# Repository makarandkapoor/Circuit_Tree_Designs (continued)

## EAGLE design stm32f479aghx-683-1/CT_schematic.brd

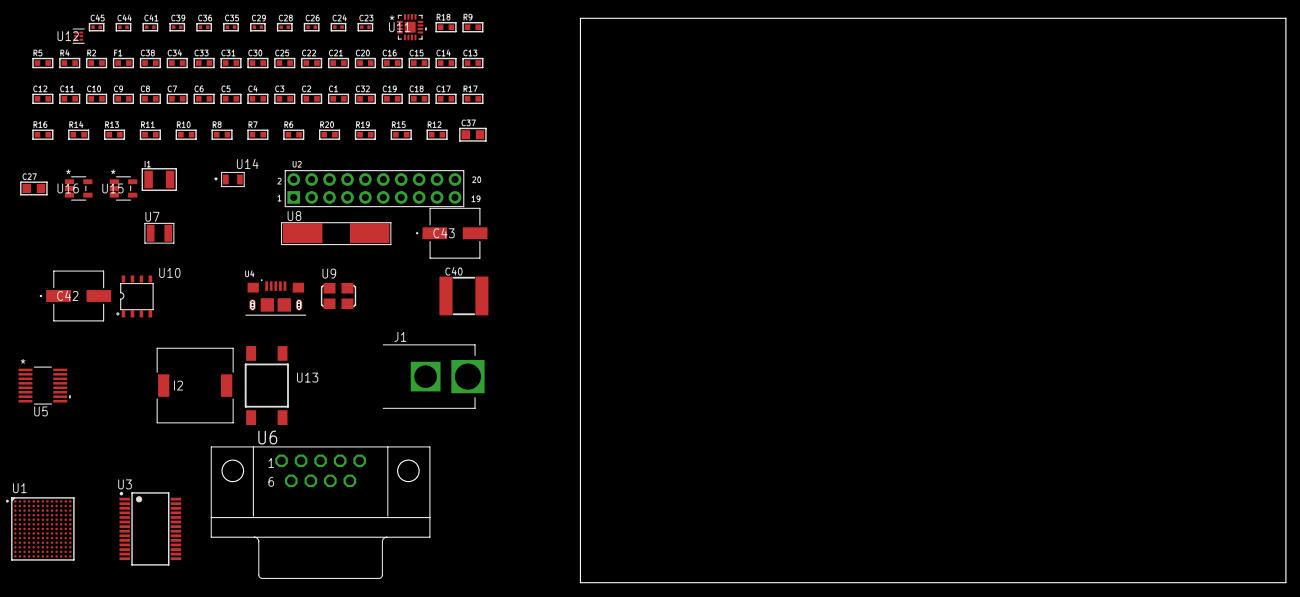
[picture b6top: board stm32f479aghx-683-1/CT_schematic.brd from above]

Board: 2 copper layers, 83 parts (0 on the bottom side), 59 nets, no tracks yet.

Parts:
C1, C21, C25, C30, C31, C33, C34, C38: 1e-06; C0603
C2, C3, C4, C5, C6, C7, C8, C9, C10, C11, C12, C13, C14, C15, C16, C22: 1e-07; C0603
C17: 4.7e-06; C0603
C18, C19: 2.2e-06; C0603
C20: 1e-08; C0603
C23, C24: 1e-11; C0402
C26, C28, C29, C39, C41: 1e-07; C0402
C27: 4.7e-06; C0805
C32: 2.2e-07; C0603
C35, C36, C44, C45: 1e-08; C0402
C37: 1e-05; C0805
C40: 6.8e-05; 2220
C42, C43: 0.0001; EXV-9H
F1: 240.0; L0603
I1: 1e-05; L1210
I2: 5.2e-06; DR1040
J1: PJ-037B; PJ-037B_PACKAGE
R2: 1000.0; R0603
R4, R5, R9: 4700.0; R0603
R6, R7, R8, R10, R11, R16, R17: 10000.0; R0603
R12: 100000.0; R0603
R13: 20000.0; R0603
R14: 91000.0; R0603
R15: 300000.0; R0603
R18: 9100.0; R0603
R19: 680000.0; R0603
R20: 120000.0; R0603
U1: STM32F479AGH6; UFBGA169
U2: arducam_ov2640; ARDUCAM
U3: FT232RL-REEL; SSOP-28
U4: 10118193-0001LF; FCI_10118193-0001LF
U5: LTC2804CGN-1#PBF; SSOP-16
U6: 182-009-113R531; 182-009-MALE
U7: ABS07-32.768KHZ-7-T
U8: ABLS-12.000MHZ-B4-T
U9: ASFL1-25MHZ-NCS; ASFL1
U10: idt74fct38072; IDT74FCT38072
U11: LTC3601EUD#PBF; QFN-16_EP
U12: TPS3895ADRYR; SON-6
U13: 4-1437565-2; SW_4-1437565-2
U14: Q65110A2395; LGM67K-G1J2-24-Z
U15, U16: nc7sz125m5x; NC7SZ125M5X

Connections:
CLK_CRYSTAL_U1_E1: C23.1, U1.E1, U7.1
CLK_CRYSTAL_U1_F1: C24.1, U1.F1, U7.2
CLK_CRYSTAL_U3_27: U3.27, U8.1
CLK_CRYSTAL_U3_28: U3.28, U8.2
CLK_U1_G2: U1.G2, U10.6
CLK_U2_8: U2.8, U10.7
CLK_U10_3: U9.3, U10.3
GND: C1.2, C2.2, C3.2, C4.2, C5.2, C6.2, C7.2, C8.2, C9.2, C10.2, C11.2, C12.2, C13.2, C14.2, C15.2, C16.2, C17.2, C18.2, C19.2, C20.2, C21.2, C22.2, C23.2, C24.2, C25.2, C26.2, C27.2, C28.2, C29.2, C30.2, C31.2, C33.2, C34.2, C35.2, C36.2, C37.2, C38.2, C40.1, C40.2, C41.2, C42.2, C43.2, C44.2, C45.2, J1.2, R2.2, R8.2, R11.2, R13.2, R15.2, R18.2, R20.2, U1.D11, U1.E3, U1.F5, U1.F8, U1.G7, U1.G9, U1.H11, U1.J1, U1.J2, U1.J6, U1.J7, U1.J10, U1.K11, U1.M9, U2.2, U2.20, U3.7, U3.18, U3.21, U3.25, U3.26, U4.5, U4.6, U4.7, U4.8, U4.9, U5.8, U6.5, U9.2, U10.4, U10.5, U10.8, U11.1, U11.9, U11.17, U12.2, U14.C, U15.1, U15.3, U16.1, U16.3
NET_U1_A5: R7.1, U1.A5
NET_U1_C3: R6.1, U1.C3
NET_U1_D12: C19.1, U1.D12
NET_U1_H2: R4.1, U1.H2, U15.4
NET_U1_J3: C20.1, C21.1, F1.1, U1.J3
NET_U1_L5: R8.1, U1.L5
NET_U1_N9: C18.1, U1.N9
NET_U1_N13: U13.3, U13.4
NET_U2_19: R5.1, U2.19, U16.4
NET_U3_14: R10.1, U3.14
NET_U3_17: C28.1, U3.17
NET_U3_19: R11.1, U3.19
NET_U4_1: R9.1, U4.1
NET_U4_2: U3.16, U4.2
NET_U4_3: U3.15, U4.3
NET_U5_6: C30.1, U5.6
NET_U5_7: C32.1, I1.2, U5.7
NET_U5_9: C31.1, U5.9
NET_U5_10: C32.2, U5.10
NET_U5_11: R12.1, U5.11
NET_U6_2: U5.1, U6.2
NET_U6_3: U5.3, U6.3
NET_U6_7: U5.2, U6.7
NET_U6_8: U5.4, U6.8
NET_U11_3: C39.2, I2.1, U11.3, U11.4
NET_U11_6: C39.1, U11.6
NET_U11_7: C38.1, U11.7, U11.12
NET_U11_10: R15.1, U11.10
NET_U11_11: R13.1, R14.1, U11.11
NET_U11_ATNET_3: I2.2, R14.2
NET_U12_1: R17.1, R18.1, U12.1
NET_U12_3: R19.2, R20.1, U12.3
NET_U12_4: R16.1, U12.4, U15.2, U16.2
NET_U13_1: R2.1, U13.1, U13.2
PROC_DCMI_D0: U1.E8, U2.18
PROC_DCMI_D1: U1.E9, U2.17
PROC_DCMI_D2: U1.A4, U2.16
PROC_DCMI_D3: U1.A3, U2.15
PROC_DCMI_D4: U1.C2, U2.14
PROC_DCMI_D5: U1.B3, U2.13
PROC_DCMI_D6: U1.A1, U2.12
PROC_DCMI_D7: U1.B1, U2.11
PROC_DCMI_D8: U1.C11, U2.10
PROC_DCMI_D9: U1.B12, U2.9
PROC_DCMI_HSYNC: U1.H8, U2.6
PROC_DCMI_PIXCLK: U1.N3, U2.7
PROC_DCMI_VSYNC: U1.A2, U2.5
PROC_UART4_RX: U1.B9, U3.1
PROC_UART4_TX: U1.C10, U3.5
VCC_S1_12V9: C37.1, C42.1, C43.1, J1.1, U11.15, U11.16
VCC_TIER1_3V3: C1.1, C2.1, C3.1, C4.1, C5.1, C6.1, C7.1, C8.1, C9.1, C10.1, C11.1, C12.1, C13.1, C14.1, C15.1, C16.1, C17.1, C22.1, C25.1, C26.1, C27.1, C29.1, C33.1, C34.1, C35.1, C36.1, C40.2, C41.1, C44.1, C45.1, F1.2, I1.1, I2.2, R4.2, R5.2, R6.2, R7.2, R10.2, R12.2, R14.2, R16.2, R17.2, R19.1, U1.D3, U1.D10, U1.E5, U1.F4, U1.F7, U1.G8, U1.G11, U1.J4, U1.K6, U1.K10, U1.K13, U1.L6, U1.L9, U2.1, U3.4, U3.20, U5.5, U5.12, U9.4, U10.1, U10.2, U11.8, U12.6, U15.5, U16.5

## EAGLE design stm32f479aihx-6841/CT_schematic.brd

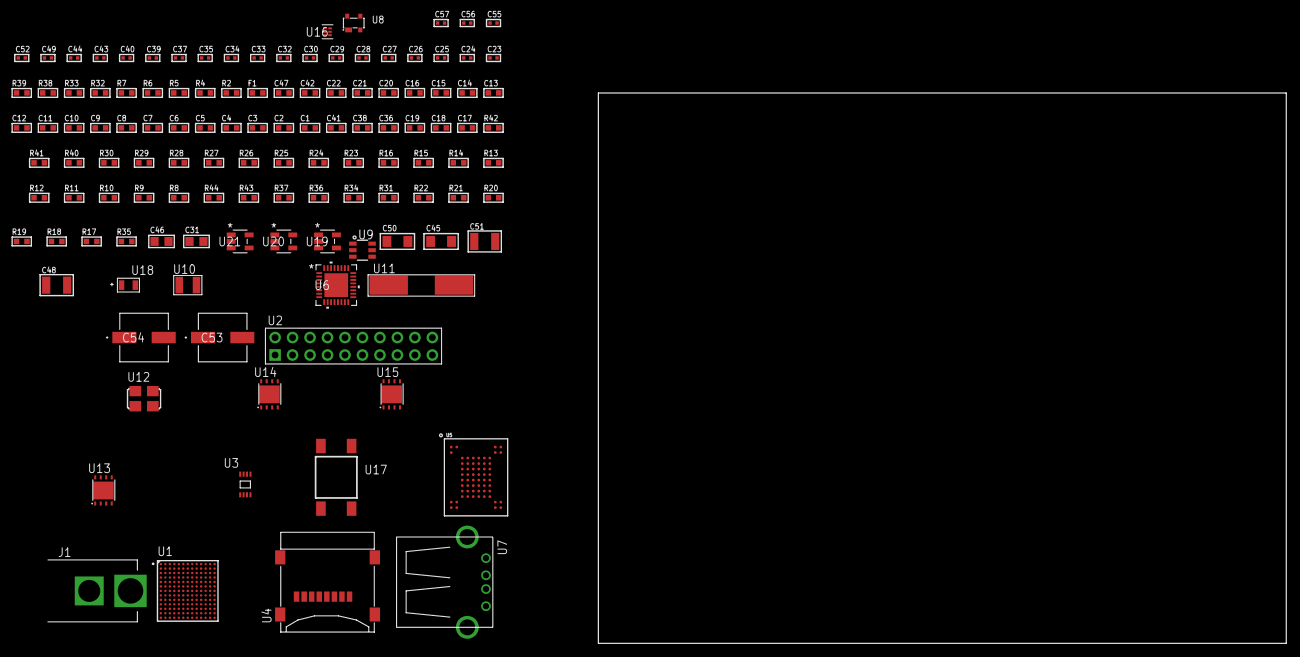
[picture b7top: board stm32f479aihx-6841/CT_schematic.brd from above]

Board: 2 copper layers, 100.0 x 80.0 mm, 122 parts (0 on the bottom side), 82 nets, no tracks yet.

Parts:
C1, C21, C47: 1e-06; C0603
C2, C3, C4, C5, C6, C7, C8, C9, C10, C11, C12, C13, C14, C15, C16, C22: 1e-07; C0603
C17: 4.7e-06; C0603
C18, C19, C36, C38, C41: 2.2e-06; C0603
C20: 1e-08; C0603
C23, C24, C25, C26: 1e-11; C0402
C27, C28, C30, C32, C33, C34, C35, C37, C39, C40, C52: 1e-07; C0402
C29, C43, C44, C49, C55, C56, C57: 1e-08; C0402
C31, C46: 1e-05; C0805
C42: 0.0001; R0603
C45, C50: 1e-05; C1206
C48, C51: 1e-05; C1210
C53, C54: 0.0001; EXV-9H
F1: 240.0; L0603
J1: PJ-037B; PJ-037B_PACKAGE
R2, R33, R39: 1000.0; R0603
R4, R5: 4700.0; R0603
R6, R7: 2200.0; R0603
R8, R9, R10, R11, R12, R13, R14, R15, R16, R23, R24, R25, R26, R27, R29, R30, R40, R41: 10000.0; R0603
R17, R18, R19, R20, R21, R22, R31, R34, R36, R37: 100000.0; R0603
R28: 47000.0; R0603
R32: 806.0; R0603
R35: 153694.38; R0603
R38: 3900.0; R0603
R42: 82000.0; R0603
R43: 300000.0; R0603
R44: 120000.0; R0603
U1: STM32F479AIH6; UFBGA169
U2: TST-110-05-T-D-RA
U3: 24AA16-I/MC; TDFN-8/6MM
U4: 0472192001; MOLEX_47219-2001
U5: mt29f4g08abbdah4; VFBGA-63
U6: TUSB1210BRHBR; RHB32_3P45X3P45
U7: 61400416021; USB-A-H
U8: prtr5v0u2ax; SOT143B
U9: MAX4995AAUT+T; SOT-23-6
U10: ABS07-32.768KHZ-7-T
U11: ABLS-25.000MHZ-B2F-T
U12: ASFL1-19.2MHZ-NCS; ASFL1
U13, U15: LP3878SDX-ADJ/NOPB; WSON-8
U14: LP2951ACSDX/NOPB; WSON-8
U16: TPS3895ADRYR; SON-6
U17: 4-1437565-2; SW_4-1437565-2
U18: Q65110A2395; LGM67K-G1J2-24-Z
U19, U20, U21: nc7sz125m5x; NC7SZ125M5X

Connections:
CLK_CRYSTAL_U1_E1: C23.1, U1.E1, U10.1
CLK_CRYSTAL_U1_F1: C24.1, U1.F1, U10.2
CLK_CRYSTAL_U1_G1: C25.1, U1.G1, U11.1
CLK_CRYSTAL_U1_G2: C26.1, U1.G2, U11.2
CLK_U6_1: U6.1, U12.3
GND: C1.2, C2.2, C3.2, C4.2, C5.2, C6.2, C7.2, C8.2, C9.2, C10.2, C11.2, C12.2, C13.2, C14.2, C15.2, C16.2, C17.2, C18.2, C19.2, C20.2, C21.2, C22.2, C23.2, C24.2, C25.2, C26.2, C27.2, C28.2, C29.2, C30.2, C31.2, C32.2, C33.2, C34.2, C35.2, C36.2, C37.2, C38.2, C39.2, C40.2, C41.2, C42.2, C43.2, C44.2, C45.2, C46.2, C47.2, C48.2, C49.2, C50.2, C51.2, C52.2, C53.2, C54.2, C55.2, C56.2, C57.2, J1.2, R2.2, R16.2, R28.2, R30.2, R33.2, R36.2, R39.2, R42.2, R44.2, U1.D11, U1.E3, U1.F5, U1.F8, U1.G7, U1.G9, U1.H11, U1.J1, U1.J2, U1.J6, U1.J7, U1.J10, U1.K11, U1.M9, U2.4, U2.6, U2.8, U2.10, U2.12, U2.14, U2.16, U2.18, U2.20, U3.4, U3.7, U4.6, U4.G1, U4.G2, U4.G3, U4.G4, U5.C5, U5.F7, U5.K3, U5.K8, U6.23, U6.33, U7.4, U7.5, U7.6, U8.1, U9.2, U12.2, U13.3, U13.PAD, U14.3, U14.4, U14.PAD, U15.3, U15.PAD, U16.2, U18.C, U19.2, U19.3, U20.1, U20.3, U21.1, U21.3
NET_U1_A5: R9.1, U1.A5
NET_U1_B4: R7.1, U1.B4, U3.5
NET_U1_C3: R8.1, U1.C3
NET_U1_C5: R6.1, U1.C5, U3.6
NET_U1_D12: C19.1, U1.D12
NET_U1_H2: R4.1, U1.H2, U20.4
NET_U1_J3: C20.1, C21.1, F1.1, U1.J3
NET_U1_L5: R10.1, U1.L5
NET_U1_N9: C18.1, U1.N9
NET_U1_N13: U17.3, U17.4
NET_U2_19: R16.1, U2.19
NET_U5_C3: R27.1, U5.C3
NET_U6_11: R29.1, U6.11
NET_U6_12: C41.1, U6.12
NET_U6_14: R30.1, U6.14
NET_U6_20: C38.1, U6.20
NET_U6_27: R5.1, U6.27, U21.4
NET_U7_1: C42.1, U6.22, U7.1, U8.4, U9.1
NET_U7_2: U6.19, U7.2, U8.3
NET_U7_3: U6.18, U7.3, U8.2
NET_U9_3: R28.1, U9.3
NET_U9_4: U6.17, U9.4
NET_U13_1: C44.1, U13.1
NET_U13_6: R32.2, R33.1, U13.6
NET_U13_8: R31.1, U13.8
NET_U14_5: R34.1, U14.5
NET_U14_7: R35.2, R36.1, U14.7
NET_U15_1: C49.1, U15.1
NET_U15_6: R38.2, R39.1, U15.6
NET_U15_8: R37.1, U15.8
NET_U16_1: R41.1, R42.1, U16.1
NET_U16_3: R43.2, R44.1, U16.3
NET_U16_4: R40.1, U16.4, U19.4, U20.2, U21.2
NET_U17_1: R2.1, U17.1, U17.2
PROC_FMC_A16: U1.M11, U5.D5
PROC_FMC_A17: U1.M13, U5.C4
PROC_FMC_D0: U1.L12, U5.H4
PROC_FMC_D1: U1.L13, U5.J4
PROC_FMC_D2: U1.C9, U5.K4
PROC_FMC_D3: U1.C7, U5.K5
PROC_FMC_D4: U1.N7, U5.K6
PROC_FMC_D5: U1.G6, U5.J7
PROC_FMC_D6: U1.H6, U5.K7
PROC_FMC_D7: U1.H7, U5.J8
PROC_FMC_INT: R23.1, U1.E11, U5.C8
PROC_FMC_NCE: R24.1, U1.E6, U5.C6
PROC_FMC_NOE: R26.1, U1.C6, U5.D4
PROC_FMC_NWE: R25.1, U1.B7, U5.C7
PROC_SDIO_CK: R18.1, U1.A9, U4.5
PROC_SDIO_CMD: R17.1, U1.B8, U4.3
PROC_SDIO_D0: R19.1, U1.E10, U4.7
PROC_SDIO_D1: R20.1, U1.G10, U4.8
PROC_SDIO_D2: R21.1, U1.C10, U4.1
PROC_SDIO_D3: R22.1, U1.B9, U4.2
PROC_SYS_JTCK_SWCLK: R14.1, U1.A10, U2.9
PROC_SYS_JTDI: R12.1, U1.B11, U2.5
PROC_SYS_JTDO_SWO: U1.B5, U2.13
PROC_SYS_JTMS_SWDIO: R13.1, U1.A11, U2.7
PROC_SYS_JTRST: R11.1, U1.D6, U2.3
PROC_USB_OTG_HS_ULPI_CK: U1.M3, U6.26
PROC_USB_OTG_HS_ULPI_D0: U1.K3, U6.3
PROC_USB_OTG_HS_ULPI_D1: U1.N4, U6.4
PROC_USB_OTG_HS_ULPI_D2: U1.K5, U6.5
PROC_USB_OTG_HS_ULPI_D3: U1.M8, U6.6
PROC_USB_OTG_HS_ULPI_D4: U1.N8, U6.7
PROC_USB_OTG_HS_ULPI_D5: U1.N10, U6.9
PROC_USB_OTG_HS_ULPI_D6: U1.N11, U6.10
PROC_USB_OTG_HS_ULPI_D7: U1.D5, U6.13
PROC_USB_OTG_HS_ULPI_DIR: U1.F2, U6.31
PROC_USB_OTG_HS_ULPI_NXT: U1.M2, U6.2
PROC_USB_OTG_HS_ULPI_STP: U1.M1, U6.29
RST_OUT_U2_SRESET_B: R15.1, U2.15, U19.1
VCC_S1_7V1: C45.1, C47.1, C50.1, C53.1, C54.1, J1.1, R31.2, R37.2, U13.4, U14.8, U15.4
VCC_TIER1_1V8: C1.1, C2.1, C3.1, C4.1, C5.1, C6.1, C7.1, C8.1, C9.1, C10.1, C11.1, C12.1, C13.1, C14.1, C15.1, C16.1, C17.1, C28.1, C29.1, C30.1, C31.1, C32.1, C33.1, C34.1, C35.1, C36.1, C39.1, C40.1, C46.1, C52.1, C55.1, C56.1, C57.1, F1.2, R4.2, R5.2, R6.2, R7.2, R8.2, R9.2, R10.2, R11.2, R12.2, R13.2, R14.2, R15.2, R17.2, R18.2, R19.2, R20.2, R21.2, R22.2, R23.2, R24.2, R25.2, R26.2, R27.2, R29.2, R32.1, R40.2, R41.2, R43.1, U1.D3, U1.D10, U1.E5, U1.F4, U1.F7, U1.G8, U1.J4, U1.K6, U1.K10, U1.K13, U1.L6, U1.L9, U2.1, U3.8, U4.4, U5.D3, U5.G4, U5.H8, U5.J6, U6.28, U6.30, U6.32, U13.5, U16.6, U19.5, U20.5, U21.5
VCC_TIER1_3V3: C22.1, C27.1, C37.1, C43.1, C48.1, R34.2, R35.1, U1.G11, U2.2, U6.21, U12.4, U14.1
VCC_TIER1_5V0: C51.1, R38.1, U9.5, U15.5

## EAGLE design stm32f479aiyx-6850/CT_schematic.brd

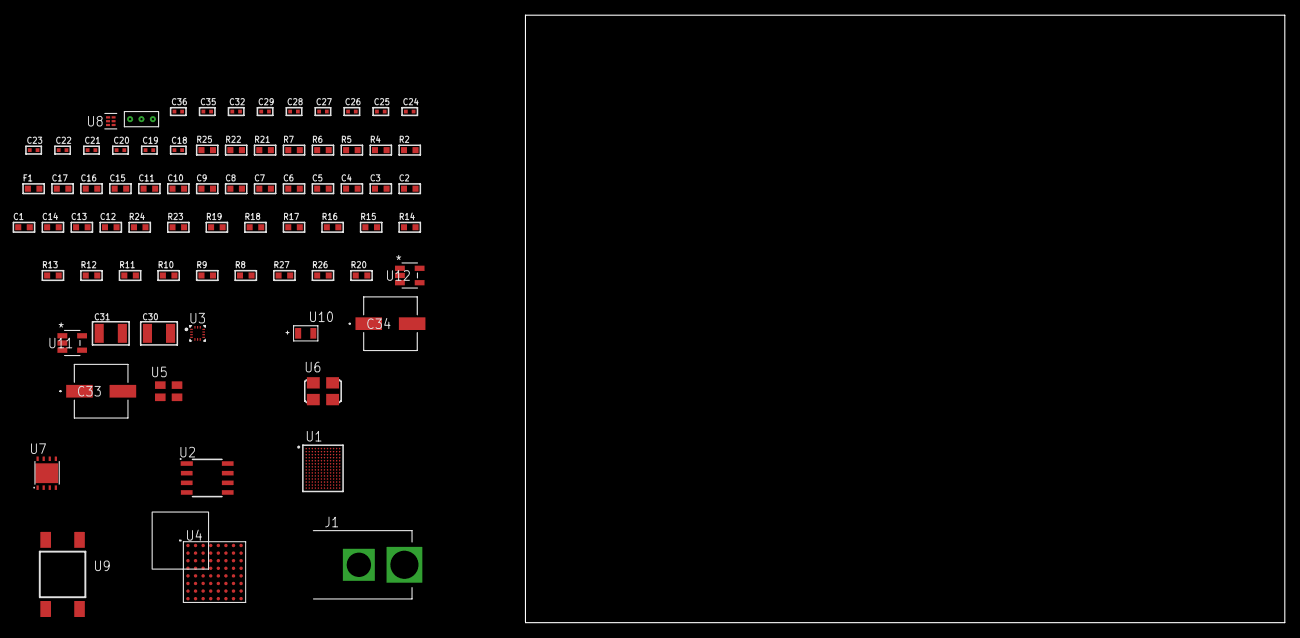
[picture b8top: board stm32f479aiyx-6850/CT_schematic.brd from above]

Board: 2 copper layers, 100.0 x 80.0 mm, 76 parts (0 on the bottom side), 80 nets, no tracks yet.

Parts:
C1, C16: 1e-06; C0603
C2, C3, C4, C5, C6, C7, C8, C9, C10, C11, C17: 1e-07; C0603
C12: 4.7e-06; C0603
C13, C14: 2.2e-06; C0603
C15: 1e-08; C0603
C18, C22, C24, C26, C27, C28, C29, C35, C36: 1e-08; C0402
C19, C20, C21, C23, C25, C32: 1e-07; C0402
C30, C31: 1e-05; C1210
C33, C34: 0.0001; EXV-9H
F1: 240.0; L0603
J1: PJ-037B; PJ-037B_PACKAGE
R2, R22: 1000.0; R0603
R4, R5: 4700.0; R0603
R6, R7: 2200.0; R0603
R8, R9, R10, R11, R12, R13, R14, R15, R16, R17, R18, R19, R23, R24: 10000.0; R0603
R20: 100000.0; R0603
R21: 2231.0; R0603
R25: 9100.0; R0603
R26: 680000.0; R0603
R27: 120000.0; R0603
U1: STM32F479AIY6TR; WLCSP168
U2: AT25010B-SSHL-T; SOIC-8
U3: BMC150; LGA14R35P5X6_200X200X100
U4: PC28F512P33BFD
U5: ASEK-32.768KHz-ECST; ASEK
U6: ASFL1-25MHZ-NCS; ASFL1
U7: LP3878SDX-ADJ/NOPB; WSON-8
U8: TPS3895ADRYR; SON-6
U9: 4-1437565-2; SW_4-1437565-2
U10: Q65110A2395; LGM67K-G1J2-24-Z
U11, U12: nc7sz125m5x; NC7SZ125M5X
U13: Dummy; DUMMY_PACKAGE_174

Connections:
CLK_U1_E11: U1.E11, U5.3
CLK_U1_K11: U1.K11, U6.3
GND: C1.2, C2.2, C3.2, C4.2, C5.2, C6.2, C7.2, C8.2, C9.2, C10.2, C11.2, C12.2, C13.2, C14.2, C15.2, C16.2, C17.2, C18.2, C19.2, C20.2, C21.2, C22.2, C23.2, C24.2, C25.2, C26.2, C27.2, C28.2, C29.2, C30.2, C31.2, C32.2, C33.2, C34.2, C35.2, C36.2, J1.2, R2.2, R10.2, R22.2, R25.2, R27.2, U1.A4, U1.B7, U1.B10, U1.C1, U1.F2, U1.F12, U1.H1, U1.H7, U1.J11, U1.L11, U1.M1, U1.N8, U1.N11, U1.P4, U2.4, U3.1, U3.6, U3.7, U3.9, U4.B2, U4.H2, U4.H4, U4.H6, U5.2, U6.2, U7.3, U7.PAD, U8.2, U10.C, U11.1, U11.3, U12.1, U12.3, U13.1
NET_U1_B9: R6.1, U1.B9, U3.11
NET_U1_D2: C14.1, U1.D2
NET_U1_D9: R8.1, U1.D9
NET_U1_E9: R7.1, U1.E9, U3.14
NET_U1_F8: R9.1, U1.F8
NET_U1_H9: R5.1, U1.H9, U12.4
NET_U1_M12: C15.1, C16.1, F1.1, U1.M12
NET_U1_N4: C13.1, U1.N4
NET_U1_P9: R10.1, U1.P9
NET_U1_P11: U9.3, U9.4
NET_U2_3: R11.1, U2.3
NET_U2_7: R13.1, U2.7
NET_U4_A4: C25.1, C26.1, U4.A4
NET_U4_C6: R18.1, U4.C6
NET_U4_D4: R4.1, U4.D4, U11.4
NET_U7_1: C29.1, U7.1
NET_U7_6: R21.2, R22.1, U7.6
NET_U7_8: R20.1, U7.8
NET_U8_1: R24.1, R25.1, U8.1
NET_U8_3: R26.2, R27.1, U8.3
NET_U8_4: R23.1, U8.4, U11.2, U12.2
NET_U9_1: R2.1, U9.1, U9.2
PROC_FMC_A0: U1.G10, U4.A1
PROC_FMC_A1: U1.H10, U4.B1
PROC_FMC_A2: U1.G12, U4.C1
PROC_FMC_A3: U1.H11, U4.D1
PROC_FMC_A4: U1.J10, U4.D2
PROC_FMC_A5: U1.H12, U4.A2
PROC_FMC_A6: U1.M8, U4.C2
PROC_FMC_A7: U1.J7, U4.A3
PROC_FMC_A8: U1.L7, U4.B3
PROC_FMC_A9: U1.H8, U4.C3
PROC_FMC_A10: U1.J6, U4.D3
PROC_FMC_A11: U1.P7, U4.C4
PROC_FMC_A12: U1.G5, U4.A5
PROC_FMC_A13: U1.G4, U4.B5
PROC_FMC_A14: U1.G2, U4.C5
PROC_FMC_A15: U1.G1, U4.D7
PROC_FMC_A16: U1.J4, U4.D8
PROC_FMC_A17: U1.M2, U4.A7
PROC_FMC_A18: U1.H4, U4.B7
PROC_FMC_A19: U1.E10, U4.C7
PROC_FMC_A20: U1.C11, U4.C8
PROC_FMC_A21: U1.B12, U4.A8
PROC_FMC_A22: U1.D11, U4.G1
PROC_FMC_A23: U1.F9, U4.H8
PROC_FMC_A24: U1.E8, U4.B6
PROC_FMC_CLK: U1.D6, U4.E6
PROC_FMC_D0: U1.L3, U4.F2
PROC_FMC_D1: U1.L2, U4.E2
PROC_FMC_D2: U1.E6, U4.G3
PROC_FMC_D3: U1.A3, U4.E4
PROC_FMC_D4: U1.N7, U4.E5
PROC_FMC_D5: U1.M7, U4.G5
PROC_FMC_D6: U1.K6, U4.G6
PROC_FMC_D7: U1.P6, U4.H7
PROC_FMC_D8: U1.N6, U4.E1
PROC_FMC_D9: U1.M6, U4.E3
PROC_FMC_D10: U1.L6, U4.F3
PROC_FMC_D11: U1.J5, U4.F4
PROC_FMC_D12: U1.P5, U4.F5
PROC_FMC_D13: U1.L4, U4.H5
PROC_FMC_D14: U1.N1, U4.G7
PROC_FMC_D15: U1.M3, U4.E7
PROC_FMC_NE2: R16.1, U1.D7, U4.B4
PROC_FMC_NL: R15.1, U1.A9, U4.F6
PROC_FMC_NOE: R17.1, U1.B4, U4.F8
PROC_FMC_NWAIT: U1.E7, U4.F7
PROC_FMC_NWE: R19.1, U1.C6, U4.G8
PROC_SPI1_MISO: U1.C8, U2.2
PROC_SPI1_MOSI: U1.B8, U2.5
PROC_SPI1_NSS: R12.1, U1.A2, U2.1
PROC_SPI1_SCK: U1.A8, U2.6
PROC_TIM1_CH1: U1.E1, U13.3
PROC_TIM1_CH2: U1.E2, U13.2
VCC_S1_15V5: C30.1, C33.1, C34.1, J1.1, R20.2, U7.4
VCC_TIER1_3V3: C1.1, C2.1, C3.1, C4.1, C5.1, C6.1, C7.1, C8.1, C9.1, C10.1, C11.1, C12.1, C17.1, C18.1, C19.1, C20.1, C21.1, C22.1, C23.1, C24.1, C27.1, C28.1, C31.1, C32.1, C35.1, C36.1, F1.2, R4.2, R5.2, R6.2, R7.2, R8.2, R9.2, R11.2, R12.2, R13.2, R14.1, R14.2, R15.2, R16.2, R17.2, R18.2, R19.2, R21.1, R23.2, R24.2, R26.1, U1.A7, U1.A11, U1.B5, U1.C2, U1.C12, U1.F1, U1.G11, U1.J12, U1.L1, U1.P3, U1.P8, U1.P12, U2.8, U3.8, U3.10, U3.12, U3.13, U4.A6, U4.D5, U4.D6, U4.G4, U4.H3, U5.4, U6.4, U7.5, U8.6, U11.5, U12.5
